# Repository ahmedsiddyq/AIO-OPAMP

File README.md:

# AIO OP-AMP

All-in-one operational-amplifier electronics project.

## Overview
This repository contains the schematic, PCB, and development files for a custom analog electronics design based around operational-amplifier circuits.

## Focus
- Analog signal conditioning
- Op-amp circuits
- PCB design
- Power supply and signal integrity
- Hardware prototyping

## Tools
- KiCad
- Analog electronics test equipment

## Author
**Ahmed Siddyq**

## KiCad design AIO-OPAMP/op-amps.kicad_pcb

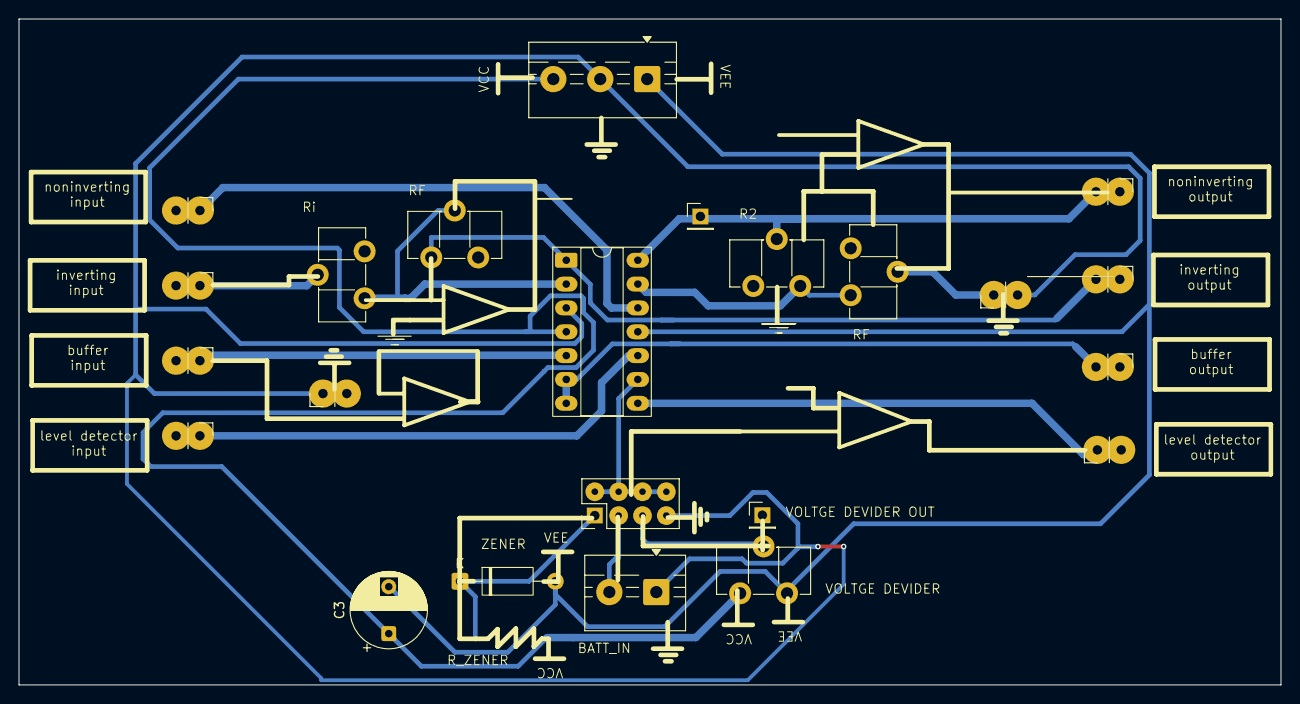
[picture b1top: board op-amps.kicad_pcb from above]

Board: 2 copper layers, 134.4 x 70.9 mm, 24 parts (1 on the bottom side), 17 nets.

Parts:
C3: C_Polarized; CP_Radial_D8.0mm_P5.00mm
D1: D_Zener_Filled; D_A-405_P10.16mm_Horizontal
J1: Screw_Terminal_01x02; TerminalBlock_MaiXu_MX126-5.0-02P_1x02_P5.00mm
J2, J5, J9, J11, J20, J21, J22, J24, J25, J26: Conn_01x02; PinHeader_1x02_P2.54mm_input
J3: Screw_Terminal_01x03; TerminalBlock_MaiXu_MX126-5.0-03P_1x03_P5.00mm
J4, J19: Conn_01x01_Pin; PinHeader_1x01_P2.54mm_Vertical
J15: Conn_02x04_Odd_Even; PinHeader_2x04_P2.54mm_Vertical
R3: R; R_Axial_DIN0207_L6.3mm_D2.5mm_P7.62mm_Horizontal
RV1, RV2, RV3, RV4, RV5: R_Potentiometer; Potentiometer_ACP_CA9-H5_Horizontal
U1: TL084; DIP-14_W7.62mm_Socket_LongPads

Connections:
unnamed: RV1.2, RV2.1, U1.2 (-)
unnamed: J15.2, J15.4, J15.6, J15.8, U1.9 (-)
unnamed: RV3.3, RV4.3, U1.13 (-)
VCC: C3.1, J3.3, R3.1, RV5.1, U1.4 (V+)
VEE: C3.2, D1.2 (A), J3.1, RV5.3, U1.11 (V-)
bat+: J1.2, J15.3
bat-: J1.1, J3.2, J15.7, J25.1, J26.1, RV3.2, U1.3 (+)
buffer_amp_vin: J5.1, U1.5 (+)
buffer_amp_vo: J11.1, U1.6 (-), U1.7
cross_detect_out: J2.1, U1.8
cross_vin: J24.1, U1.10 (+)
inv_amp_vin: J20.1, RV2.2
inv_amp_vo: J21.1, RV1.1, U1.1
noninv_amp_vin: J9.1, U1.12 (+)
noninv_amp_vo: J4.1, J22.1, RV4.2, U1.14
v_devider: J15.5, J19.1, RV5.2
v_zener: D1.1 (K), J15.1, R3.2

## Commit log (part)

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2025-12-21 in_layout
2025-12-21 starting
2025-12-21 befor flp
2025-12-22 final_nopins
2025-12-23 doin
